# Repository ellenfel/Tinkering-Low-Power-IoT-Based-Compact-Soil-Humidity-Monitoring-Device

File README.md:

# Tinkering-Low-Power-IoT-Based-Compact-Soil-Humidity-Monitoring-Device
cant get more self explanatory than that name but i will try

There is multiple designs in this repo with different design choices so as a starter

## Simple humidity detector

  Basicly we use L7805 to voltage regulator to get a constant 5V voltage. Out pin of regulator is first connected to our resistive probe then base of BC547 transistor again we paraler connect the same  Out pin of regulator to a LED and from there the collector pin of the same BC547 resistor.
  The idea here is, if current wouldn't flow throug our resistive probe; our led won't light up. which would indicate our probe is embedded in dry soil, acourding to a resistive treshold.
  We also added a 50k potentiometer between base of our transistor and ground as a way to control this threshold.

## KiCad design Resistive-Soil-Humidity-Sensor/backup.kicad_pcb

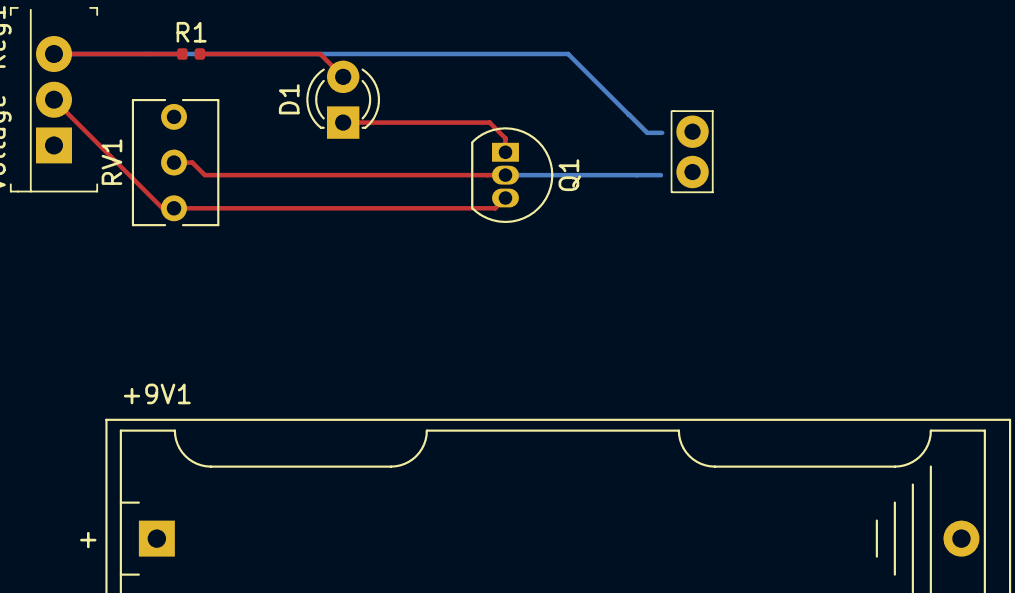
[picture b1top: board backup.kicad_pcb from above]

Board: 2 copper layers, 8 parts (0 on the bottom side), 6 nets.

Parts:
+9V1: Battery; BatteryHolder_Keystone_2466_1xAAA
D1: LED; LED_D3.0mm_FlatTop
H1, H2: MountingHole; MountingHole.1.8mm
Q1: BC547; TO-92_Inline
R1: 1kohm; R_0402_1005Metric
RV1: R_POT; Potentiometer_Bourns_3266Y_Vertical
Voltage-Reg1: L7805CV; TO-220-3

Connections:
unnamed: +9V1.1, Voltage-Reg1.1
unnamed: +9V1.2, Q1.3, RV1.3, Voltage-Reg1.2
unnamed: R1.1, Voltage-Reg1.3
unnamed: D1.1, Q1.1
unnamed: D1.2, R1.2
unnamed: Q1.2, RV1.2

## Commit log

2022-11-19 Initial empty commit
2022-11-20 finish with sch
2022-11-25 add report.txt file
2022-11-25 add pcb-layout
2022-11-25 add folder for figures
2022-11-25 add figures
2022-11-25 add sch figure
2022-11-25 pull from repo
2022-11-25 start the new project
2022-11-25 start sch of esp based circuit
2022-11-26 finish application center schematic
2022-11-26 finish usb to uart sch
2022-11-26 finish USB Section
2022-11-26 finish Battery management
2022-11-26 finish Reverse Polarity Protection
2022-12-04 add the ss of circuit. schematic to pdf doesnt work for some reason
2022-12-05 replaced a figure
2022-12-06 replace a figure
2022-12-11 update footprints & recover design
2022-12-12 dont know what happend
2022-12-13 update the design for new power supply
2022-12-13 update the backups
2022-12-14 before print changes 2
2022-12-14 before print changes 3 delete the svg files
2022-12-14 before print changes 3 install updated the svg files
2022-12-14 before print changes 4 delete unneeded svg files
2022-12-14 add pdf of layout
2022-12-23 add new pcb layout pdf's
2023-01-12 added buzzer
2024-01-17 renewed the pcb layer
    renewed the pcb layer
2024-01-18 added windows
2024-10-23 closing the project
